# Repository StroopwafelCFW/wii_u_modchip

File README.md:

# wii_u_modchip

A (WIP) Wii U modchip based on de_Fuse, a flaw in the Wii U's OTP eFuse readout state machine.

## How does it work?
A full writeup is available [here](https://douevenknow.us/post/714056575412764672/defuse-the-one-true-pwn). However, the short version is as follows:

In order to accommodate eFuse-based JTAG lockout (and due to other considerations), eFuse bits must be buffered into a register file immediately following NRST, before the internal reset can be released. The eFuse sense state machine latches at a rate of 4 bits per cycle, directly off the 27MHz XTALCLK. Every other rising edge, a byte is written into the register file, starting from the least significant byte of the current u32.

An internal counter is used to keep track of the remaining bytes to be read into the register file. While the eFuse register file is reset to zero with NRST, the internal counter is not: By asserting NRST after N bytes have been read, only 0x400-N bytes will be read on the subsequent boot.

By asserting NRST just before the final byte has been read (1830 cycles), all eFuses will read entirely zero, including the JTAG lockout fuse. This allows trivial, unsigned and unencrypted boot1 execution, with no SEEPROM anti-rollback.

## Serial-only Pico firmware (e.g. for ISFShax consoles)

Build and flash the `pico_serial` firmware. It's the same serial bridge, but without de_Fuse.
Baud 1201 resets the console and baud 1200 reboots the Pico into BOOTSEL.

    (cd pico_defuse && ./build.sh pico_serial)   # or: ./picoterm.py flash-pico  (uses pico_defuse/build/pico_serial.uf2)

## Dev workflow with `picoterm.py`

Run `./picoterm.py term` in place of minicom. Only one program can read the Pico's tty,
so the terminal owns it. The other subcommands drive the console through its control
socket (`$XDG_RUNTIME_DIR/picoterm.sock`, or `$PICOTERM_SOCK`). If no terminal is running,
they open the port themselves.

    ./picoterm.py term                          # Ctrl-T h for help, Ctrl-] to quit
    ./picoterm.py reset                         # Pico pulses NRST -> ISFShax -> minute
    ./picoterm.py plugin a.ipx b.ipx            # reset, upload to sdmc:/wiiu/ios_plugins/, boot menu entry 3
    ./picoterm.py plugin --rm old.ipx new.ipx   # delete and upload in one go
    ./picoterm.py plugin a.ipx --boot 0         # ...and stay in minute
    ./picoterm.py plugins                       # list sdmc:/wiiu/ios_plugins
    ./picoterm.py fw fw.img                     # reset, upload sdmc:/fw.img, reload it
    ./picoterm.py console                       # reset and open minute's interactive console
    ./picoterm.py send "smc read 0x40"          # type a line into minute's console

Options:
* `--no-reset` when minute is already running.
* `-f` to keep following the output.
* `--port` (or `$PICOTERM_PORT`) to override the autodetected
  `/dev/serial/by-id/usb-Raspberry_Pi_Pico_*`.

Uploading needs minute's `upload <path>` command, and deleting and listing need its `rm` and `ls`
commands, so install a current minute `fw.img` first. `picoterm.py fw` also works with older minute builds.

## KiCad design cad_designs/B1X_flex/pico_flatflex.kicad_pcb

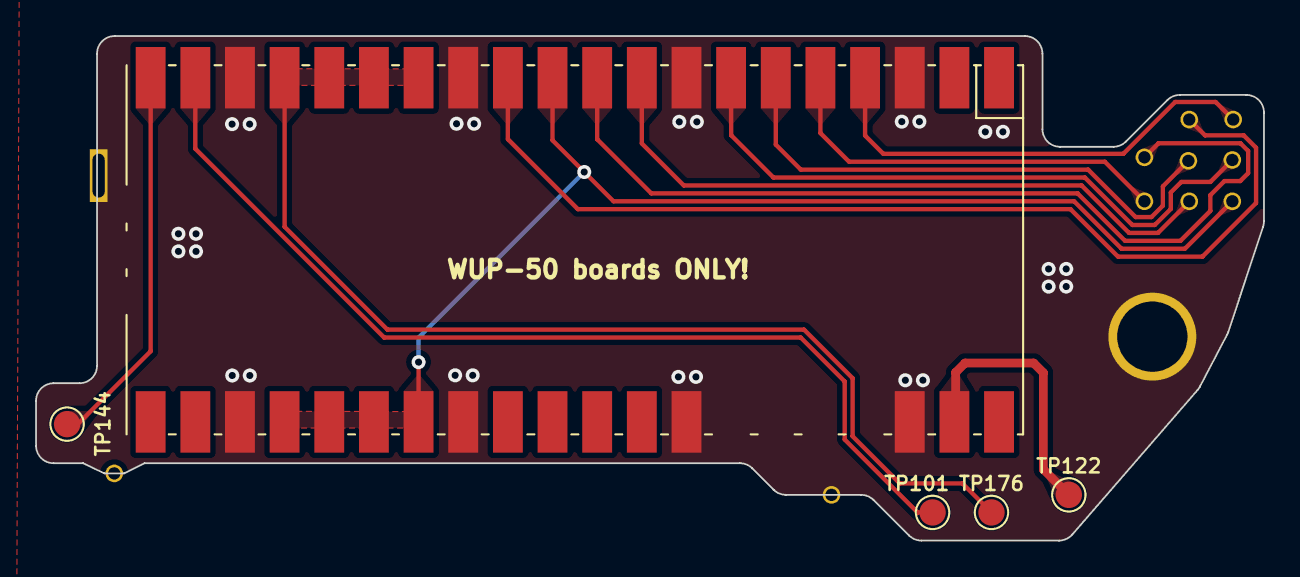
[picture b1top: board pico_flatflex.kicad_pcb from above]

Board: 2 copper layers, 69.8 x 28.7 mm, 6 parts (0 on the bottom side), 7 nets.

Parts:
J32: Conn_01x01; wii-single-via-0.5mm
TP101: EXI CLK; TestPoint_Pad_D1.5mm
TP122: 3v3; TestPoint_Pad_D1.5mm
TP144: nRST; TestPoint_Pad_D1.5mm
TP176: EXI MISO; TestPoint_Pad_D1.5mm
U1: Pico; RPi_Pico_SMD

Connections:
+3V3: TP122.1, U1.39 (VSYS)
D6: U1.11 (GPIO8), U1.24 (GPIO18), U1.25 (GPIO19), U1.26 (GPIO20), U1.27 (GPIO21)
D7: J32.1, U1.12 (GPIO9)
EXI CLK: TP101.1, U1.19 (GPIO14)
EXI MISO: TP176.1, U1.14 (GPIO10), U1.15 (GPIO11), U1.16 (GPIO12), U1.17 (GPIO13)
GND: U1.3 (GND), U1.8 (GND), U1.13 (GND), U1.18 (GND), U1.23 (GND), U1.28 (GND), U1.33 (AGND), U1.38 (GND)
nRST: TP144.1, U1.20 (GPIO15)

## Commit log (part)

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2023-04-06 cleanup
2023-04-07 Serial, and insert reset at the JTAG fuse load instead of ~0x40 bytes in
2023-04-07 More notes
2023-04-08 boot1 dumping
2023-04-16 Update w/ consistency improvements and docs
2023-04-16 Attempted to add uart rx input (Wii U drive strength is too high), watch for NRSTs and intercept them
2023-04-20 WIP pico firmware: it can read the DEBUG pins via PIO
2023-04-20 EXI inject working
2023-04-20 pico gets code exec now
2023-04-21 working serial console
2023-04-21 Dockclock to rated ranges lol
2023-04-21 wiring
2023-04-21 oops: wiring for real
2023-04-21 Asdf
2023-04-21 pico: NRST monitoring state machine
2023-04-21 Fix EXI clobbering minute_minute's reads and cleanup
2023-04-22 Serial console input, normal boot fallback
2023-04-23 Add safety for if the console is unplugged during de_Fusing
2023-04-23 More power checks
2023-04-23 oops, found the right voltage line
2023-04-23 Additional notes on wiring
2023-04-24 serial fw upload
2023-04-24 Faster serial and more reliable serial input
2023-04-25 OTP dumping
2023-04-25 Use env vars for file upload, also oops I forgot the license
2023-04-27 Byte-accurate OTP defusing on Pico
2023-05-18 wafel_core.ipx upload
2023-07-21 Do two de_Fuses per width and attempt to load boot1 from vWii NAND every other de_Fuse
2023-07-27 Fix SD detection
2023-08-10 add wiring diagram
2023-08-10 Show wiring diagram in README.md
2023-08-10 Update README.md
    put thanks into paranthesis
2023-08-16 boot1 flashing via miniterm
2023-08-16 Improve PRSHhax success maybe
2023-08-27 Add support for the Waveshare tiny board
    Note that I'm not experienced with cmake, so I don't know how to add an argument to the build script for this
2023-10-23 Pico flatflex CAD files
2024-01-27 Fix RTC reading 00s on SLC booting sometimes
2025-01-16 Add flex for WUP-50s
2025-01-16 Renamed to A5X_flex
2025-01-16 Add credits and WUP-50 warning
